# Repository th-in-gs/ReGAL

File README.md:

# ReGAL

ReGAL is a set of scripts used to assist reverse engineering of old-school
*Programmable Array Logic* devices.

## Synthesis / Place-and-route

From a verilog design, ReGAL can generate JEDEC files that can be used to
program *Generic Array Logic* devices.

The synthesis is assisted by Yosys while the place-and-route logic has been
implemented from scratch (since trivial for this type of devices).

As an example, consider the following design:

```verilog
module top (
    input a, b, c,
    output x, y, z
);

assign x = a ^ b;
assign y = ~x;
assign z = ~(c & b);

endmodule
```

From this verilog file, the netlist can be generated using the `synth`
subcommand. Internally, this command defines the GAL logic cells and configures
Yosys to parse the design file, apply high-level optimizations, perform the
technology mapping and output the netlist as a JSON file:

```console
$ regal synth -o netlist.json basic.v
```

A JEDEC file is obtained from this netlist using the `pnr` subcommand. This
step requires to specify the targeted device and the IO mapping.

```yaml
device: GAL16V8
mode: simple
pins:
    a: 1
    b: 2
    c: 3

    x: 19
    y: 18
    z: 17
```

```console
$ regal pnr -o basic.jed device.yaml netlist.json
```

The `build` subcommand combines the synthesis and the place-and-route in only
one step:

```console
$ regal build -o basic.jed device.yaml basic.v
```

It is also allowed to synthesize sequential designs if the device has been
configured in registered mode in the place-and-route configuration file:

```yaml
device: GAL16V8
mode: registered
pins:
    Clk: 1
    A: 2
    B: 3

    X: 19
    Clk2: 17
```

Due to the limitations of GAL devices, the design can only define sequential
logic on the positive edge of the dedicated clock input (Pin 1 for GAL16V8):

```verilog
module top (
    input Clk,
    input A,
    input B,

    output X,
    output reg Clk2
);

assign X = A ^ B;

always @(posedge Clk)
  Clk2 <= ~Clk2
;

endmodule
```

### Internal signals

Intermediate logic that is not assigned to a pin in the configuration file
is inlined into the macro cells that use it whenever the result still fits
(after minimization, possibly using the complement through the output XOR).

What cannot be inlined, such as internal registers or functions with more
product terms than a macro cell can hold, is automatically placed on spare
macro cells whose output feeds back into the AND-array. Oversized functions
are split, with some of their terms moved to spare macro cells. The output
pins of these macro cells are driven, so they must be left unconnected:

```console
[WARN ][regal_pnr] Internal signal Clk2 placed on spare pin 12 (leave this pin unconnected)
[WARN ][regal_pnr] Internal signal RR_part0 placed on spare pin 12 (leave this pin unconnected)
```

### Tri-state outputs

In complex mode, and for combinational outputs in registered mode, an output
can be tri-stated with `assign Y = OE ? A : 1'bz;`. The output enable gets a
single product term of its own, so `OE` must be an AND of inputs and their
complements.

### Supported devices

- GAL16V8 (simple, complex and registered mode)
- GAL20V8 (simple mode only)

## Reverse engineering locked PAL/GAL

Another aspect of this project consists in facilitating the reproduction of
locked PAL devices.
When the fuse map is not readable anymore using the standard programming
method, one alternative consists in dumping the truth tables by probing the
outputs of the device when applying all the possibles input combinations.

Obviously, this method is limited to devices implementing combinational
logic (PAL working in registered mode are out-of-scope for this
proof-of-concept).

The current implementation uses an arduino mega to drive the device under test.
The setup required to perform the IO probing on the example defined above can
be described as follow:

```yaml
probe: arduino_mega
outfile: basic_tt.csv
device: /dev/ttyUSB0

ios:
    inputs:
        - a: C0
        - b: C1
        - c: C2

    outputs:
        - x: A0
        - y: A1
        - z: A2
```

```console
$ regal dump dump.yaml
```

While controlling the probe device, the `dump` subcommand produces the
truth-table as a CSV file:

```csv
a,b,c,,x,y,z
0,0,0,,0,1,1
1,0,0,,1,0,1
0,1,0,,1,0,1
1,1,0,,0,1,1
0,0,1,,0,1,1
1,0,1,,1,0,1
0,1,1,,1,0,0
1,1,1,,0,1,0
```

Once the truth-table extracted, it can be simplified and converted to a verilog
file with the `tt2v` subcommand:

```console
$ regal tt2v basic_tt.csv basic_from_tt.v
```

The produced verilog is similar to the one used for the synthesis and can be
used to generate a new JEDEC file equivalent to the original one.

```verilog
module top (
    input a,
    input b,
    input c,
    output x,
    output y,
    output z
);

assign x =
  (~a & b) |
  (a & ~b)
;

assign y =
  (~a & ~b) |
  (a & b)
;

assign z =
  (~c) |
  (~b)
;

endmodule
```

## Installation

```console
$ pip install ./ --user
```

### Requirements

- [yosys](https://github.com/YosysHQ/yosys)
- [quine-mccluskey](https://github.com/tpircher/quine-mccluskey)

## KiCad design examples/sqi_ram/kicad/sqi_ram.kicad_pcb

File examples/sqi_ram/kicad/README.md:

# KiCad project

`sqi_ram.kicad_sch` is the interface as a KiCad 7 schematic, which KiCad 8
and 9 also open, and `sqi_ram.kicad_pcb` is a ready-routed board for it.
All parts are through-hole DIP packages, with sockets for the two GALs so
they can be reprogrammed.

## Opening it

Open `sqi_ram.kicad_pro` in KiCad. The symbols are embedded in the
schematic. The 23LC512, which the KiCad libraries lack, is also in the
project library `sqi_ram.kicad_sym`, which `sym-lib-table` adds.

Nets that connect to the 8052 use global labels:

| Label | Connect to |
|---|---|
| `AD0`-`AD7` | P0 |
| `A0`-`A7` | the outputs of the 8052's address latch |
| `A8`-`A15` | P2 |
| `~{RD}`, `~{WR}` | P3.7 and P3.6 |
| `CPUCLK` | XTAL1. Remove the crystal and its capacitors; on a CMOS 80C52 leave XTAL2 open (an NMOS 8052 is driven on XTAL2 instead) |
| `VCC`, `GND` | 5 V supply |

There are two ways to use it:

- **Add it to an existing design.** In the existing schematic, add a
  hierarchical sheet that uses `sqi_ram.kicad_sch`, and copy
  `sqi_ram.kicad_sym` and its `sym-lib-table` entry into that project.
  Global labels connect by name, so either name the 8052's nets as above or
  rename the labels here.
- **Use the board below.** It is a separate module that connects to the
  8052 board through the J1 header.

If you change the schematic, run Tools > Update PCB from Schematic (F8) in
the PCB editor: the footprints are linked to their symbols. Keep the
32 MHz oscillator, U1, SCK and the 23LC512 close together, and each chip's
100 nF capacitor right at its supply pins.

## PCB

`sqi_ram.kicad_pcb` is a 95 × 72 mm two-layer board, all through-hole,
with M3 mounting holes in the corners and ground pours on both sides.
`sqi_ram-gerbers.zip` holds the Gerbers and Excellon drill files to upload
to a board house.

| Rule | Value |
|---|---|
| Signal tracks | 0.25 mm |
| VCC and GND tracks | 0.5 mm |
| Clearance | 0.2 mm |
| Vias | 0.7 mm (0.35 mm drill), 0.8 mm (0.4 mm drill) on supplies |

Any standard two-layer service can make it.

The 8052 connects through J1, a 2×16 pin header:

| J1 pins | Signal |
|---|---|
| 1, 32 | VCC |
| 2, 29, 31 | GND |
| 3-10 | AD0-AD7 (P0) |
| 11-18 | A0-A7 (address latch outputs) |
| 19-26 | A8-A15 (P2) |
| 27, 28 | `/RD`, `/WR` |
| 30 | CPUCLK (to XTAL1), between two grounds |

Keep the cable to the 8052 board short (10 cm or less): it carries the
16 MHz clock and the data bus.

KiCad's DRC on the board finds no violations and no unconnected pads, and
every pad's net matches the schematic's netlist. The tracks are an
autorouter's: they work, but you may want to tidy them in KiCad.

### Rebuilding the board

```console
python make_pcb.py place     # unrouted board and sqi_ram.dsn
FREEROUTING_JAR=freerouting.jar python make_pcb.py route
python make_pcb.py import    # tracks from sqi_ram.ses, ground pours, DRC
```

`route` runs [Freerouting](https://freerouting.app) (2.5 needs Java 25) with
automatic neck-down off, so that every track keeps its net class width.
`import` reads Freerouting's session file and adds the ground pours. Where
the tracks leave room for only one thermal spoke, it connects the pad to
the pour solidly. `sqi_ram.ses` is committed, so `import` alone rebuilds
this board.

## Parts

| Ref | Part | Notes |
|---|---|---|
| U1 | GAL16V8 or ATF16V8B, 15 ns or faster | Sequencer: program with `../seq.jed` |
| U2 | GAL16V8 or ATF16V8B, 15 ns or faster | SIO driver: program with `../sio.jed` |
| U3 | 74AC138 or 74ACT138 | Not HC: the address enable path is timing-critical |
| U4, U5 | 74AC244 or 74ACT244 | Not HC, as above |
| U6 | 74AC574 or 74ACT574 | |
| U7 | 23LC512-I/P | 64 KB SPI/SQI SRAM, DIP-8 |
| X1 | 32 MHz oscillator, DIP-8 can, 5 V | |
| R1-R4 | 10 kΩ | SIO pull-ups |
| J1 | 2×16 pin header, 2.54 mm | To the 8052 board |
| C1-C7 | 100 nF | Decoupling |

GAL16V8s from Lattice are no longer made. The Microchip (Atmel) ATF16V8B is
the current equivalent and takes the same JEDEC files. Choose 10 ns parts
if you can: with 15 ns parts the address path has only about 4 ns to spare
at 32 MHz. Programmers such as the TL866II+ and T48 handle both.

## Software

The first `MOVX` after power-up must switch the RAM to SQI mode:

```asm
        MOV     DPTR, #9998h
        MOV     A, #88h
        MOVX    @DPTR, A
```

See `../README.md` for how the design works and its limitations.

## Regenerating

`make_schematic.py` writes the schematic from `../seq.yaml`, `../sio.yaml`
and `../encoding.py`. `check_schematic.py` exports the netlist with
`kicad-cli` and checks it against the design. It verifies:

- every pin's net
- that unused pins are only the intended ones
- footprint pads
- that each address nibble reaches SIO0-3 in bit order at the nibble number
  where the sequencer expects it
- the 74AC574 shift path
- the 23LC512 pinout

If you edit the schematic by hand, check it again with
`python check_schematic.py`.

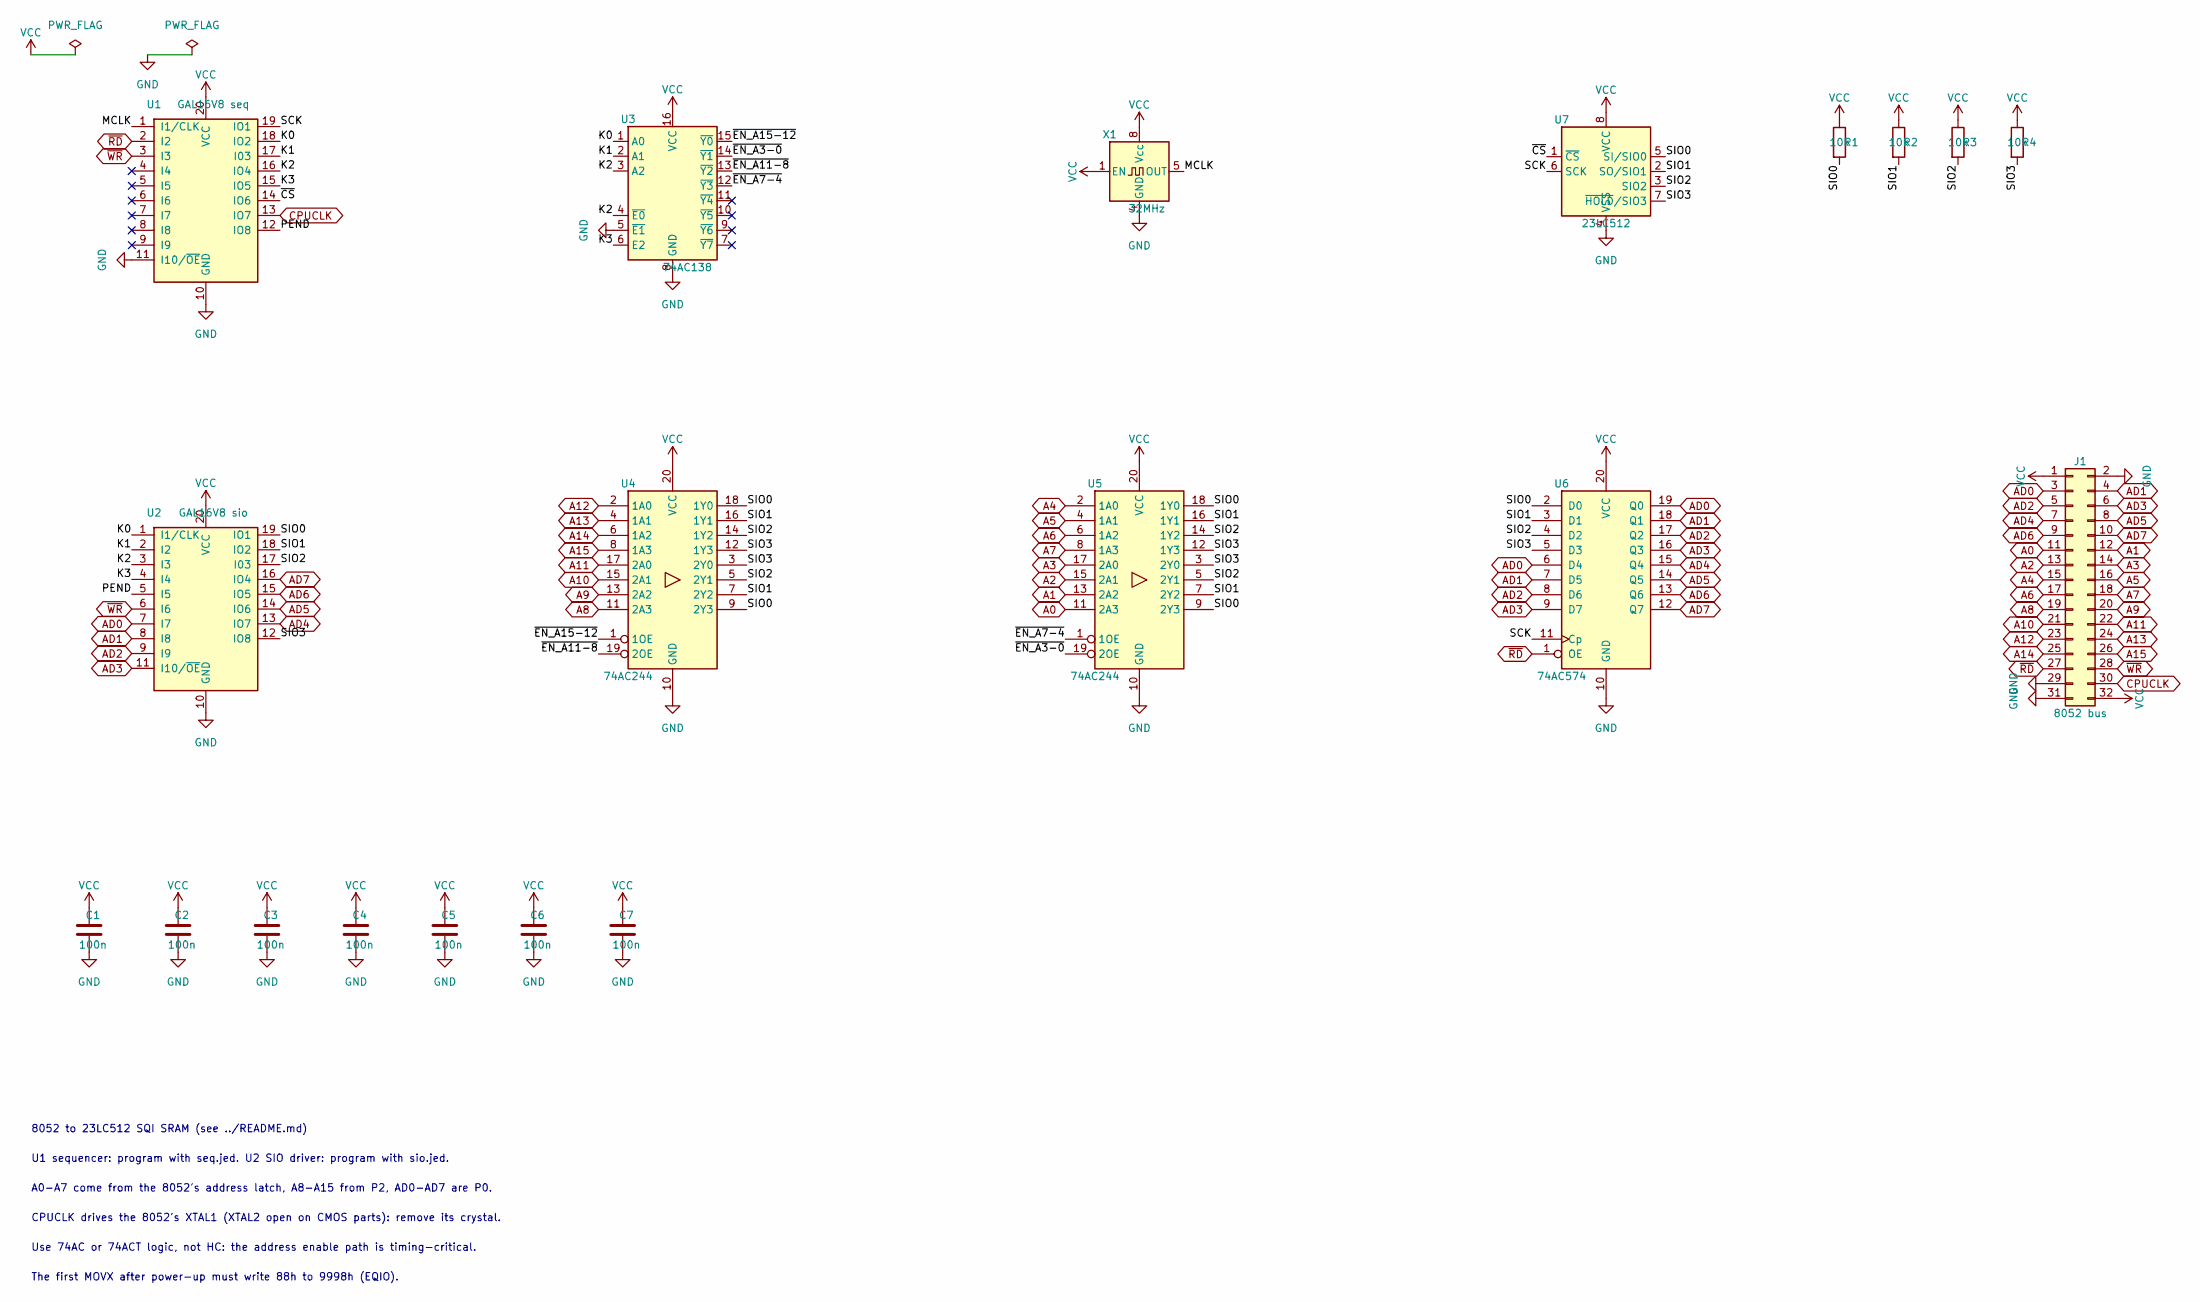
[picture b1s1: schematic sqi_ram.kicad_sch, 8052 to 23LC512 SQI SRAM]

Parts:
C1, C2, C3, C4, C5, C6, C7: 100n; C_Disc_D5.0mm_W2.5mm_P5.00mm
J1: 8052 bus; PinHeader_2x16_P2.54mm_Vertical
R1, R2, R3, R4: 10k; R_Axial_DIN0207_L6.3mm_D2.5mm_P7.62mm_Horizontal
U1: GAL16V8 seq; DIP-20_W7.62mm_Socket
U2: GAL16V8 sio; DIP-20_W7.62mm_Socket
U3: 74AC138; DIP-16_W7.62mm
U4, U5: 74AC244; DIP-20_W7.62mm
U6: 74AC574; DIP-20_W7.62mm
U7: 23LC512; DIP-8_W7.62mm
X1: 32MHz; Oscillator_DIP-8

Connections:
/K0: U1.18 (IO2), U2.1 (I1/CLK), U3.1 (A0)
/K1: U1.17 (I03), U2.2 (I2), U3.2 (A1)
/K2: U1.16 (IO4), U2.3 (I3), U3.3 (A2), U3.4 (~E0)
/K3: U1.15 (IO5), U2.4 (I4), U3.6 (E2)
/MCLK: U1.1 (I1/CLK), X1.5 (OUT)
/PEND: U1.12 (IO8), U2.5 (I5)
/SCK: U1.19 (IO1), U6.11 (Cp), U7.6 (SCK)
/SIO0: R1.2, U2.19 (IO1), U4.9 (2Y3), U4.18 (1Y0), U5.9 (2Y3), U5.18 (1Y0), U6.2 (D0), U7.5 (SI/SIO0)
/SIO1: R2.2, U2.18 (IO2), U4.7 (2Y2), U4.16 (1Y1), U5.7 (2Y2), U5.16 (1Y1), U6.3 (D1), U7.2 (SO/SIO1)
/SIO2: R3.2, U2.17 (I03), U4.5 (2Y1), U4.14 (1Y2), U5.5 (2Y1), U5.14 (1Y2), U6.4 (D2), U7.3 (SIO2)
/SIO3: R4.2, U2.12 (IO8), U4.3 (2Y0), U4.12 (1Y3), U5.3 (2Y0), U5.12 (1Y3), U6.5 (D3), U7.7 (~HOLD/SIO3)
/~CS: U1.14 (IO6), U7.1 (~CS)
/~EN_A3-0: U3.14 (~Y1), U5.19 (2OE)
/~EN_A7-4: U3.12 (~Y3), U5.1 (1OE)
/~EN_A11-8: U3.13 (~Y2), U4.19 (2OE)
/~EN_A15-12: U3.15 (~Y0), U4.1 (1OE)
A0: J1.11, U5.11 (2A3)
A1: J1.12, U5.13 (2A2)
A2: J1.13, U5.15 (2A1)
A3: J1.14, U5.17 (2A0)
A4: J1.15, U5.2 (1A0)
A5: J1.16, U5.4 (1A1)
A6: J1.17, U5.6 (1A2)
A7: J1.18, U5.8 (1A3)
A8: J1.19, U4.11 (2A3)
A9: J1.20, U4.13 (2A2)
A10: J1.21, U4.15 (2A1)
A11: J1.22, U4.17 (2A0)
A12: J1.23, U4.2 (1A0)
A13: J1.24, U4.4 (1A1)
A14: J1.25, U4.6 (1A2)
A15: J1.26, U4.8 (1A3)
AD0: J1.3, U2.7 (I7), U6.6 (D4), U6.19 (Q0)
AD1: J1.4, U2.8 (I8), U6.7 (D5), U6.18 (Q1)
AD2: J1.5, U2.9 (I9), U6.8 (D6), U6.17 (Q2)
AD3: J1.6, U2.11 (I10/~OE), U6.9 (D7), U6.16 (Q3)
AD4: J1.7, U2.13 (IO7), U6.15 (Q4)
AD5: J1.8, U2.14 (IO6), U6.14 (Q5)
AD6: J1.9, U2.15 (IO5), U6.13 (Q6)
AD7: J1.10, U2.16 (IO4), U6.12 (Q7)
CPUCLK: J1.30, U1.13 (IO7)
GND: C1.2, C2.2, C3.2, C4.2, C5.2, C6.2, C7.2, J1.2, J1.29, J1.31, U1.10 (GND), U1.11 (I10/~OE), U2.10 (GND), U3.5 (~E1), U3.8 (GND), U4.10 (GND), U5.10 (GND), U6.10 (GND), U7.4 (VSS), X1.4 (GND)
VCC: C1.1, C2.1, C3.1, C4.1, C5.1, C6.1, C7.1, J1.1, J1.32, R1.1, R2.1, R3.1, R4.1, U1.20 (VCC), U2.20 (VCC), U3.16 (VCC), U4.20 (VCC), U5.20 (VCC), U6.20 (VCC), U7.8 (VCC), X1.1 (EN), X1.8 (Vcc)
~RD: J1.27, U1.2 (I2), U6.1 (OE)
~WR: J1.28, U1.3 (I3), U2.6 (I6)

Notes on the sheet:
8052 to 23LC512 SQI SRAM (see ../README.md)
U1 sequencer: program with seq.jed. U2 SIO driver: program with sio.jed.
A0-A7 come from the 8052's address latch, A8-A15 from P2, AD0-AD7 are P0.
CPUCLK drives the 8052's XTAL1 (XTAL2 open on CMOS parts): remove its crystal.
Use 74AC or 74ACT logic, not HC: the address enable path is timing-critical.
The first MOVX after power-up must write 88h to 9998h (EQIO).

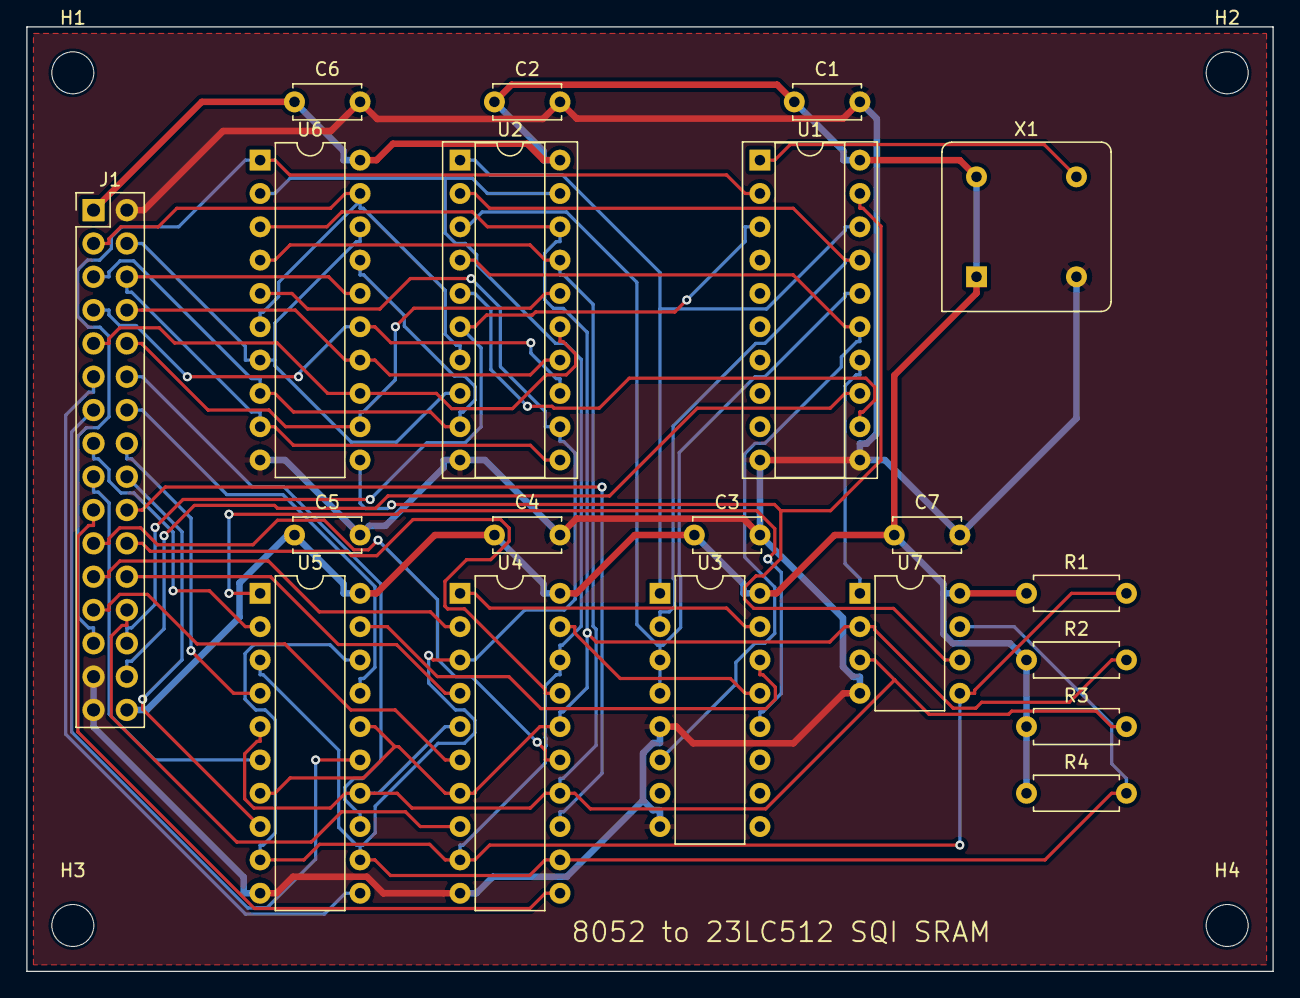
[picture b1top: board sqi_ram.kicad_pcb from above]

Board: 2 copper layers, 95.0 x 72.0 mm, 24 parts (0 on the bottom side), 45 nets.

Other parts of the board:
H1, H2, H3, H4: MountingHole_3.2mm_M3
